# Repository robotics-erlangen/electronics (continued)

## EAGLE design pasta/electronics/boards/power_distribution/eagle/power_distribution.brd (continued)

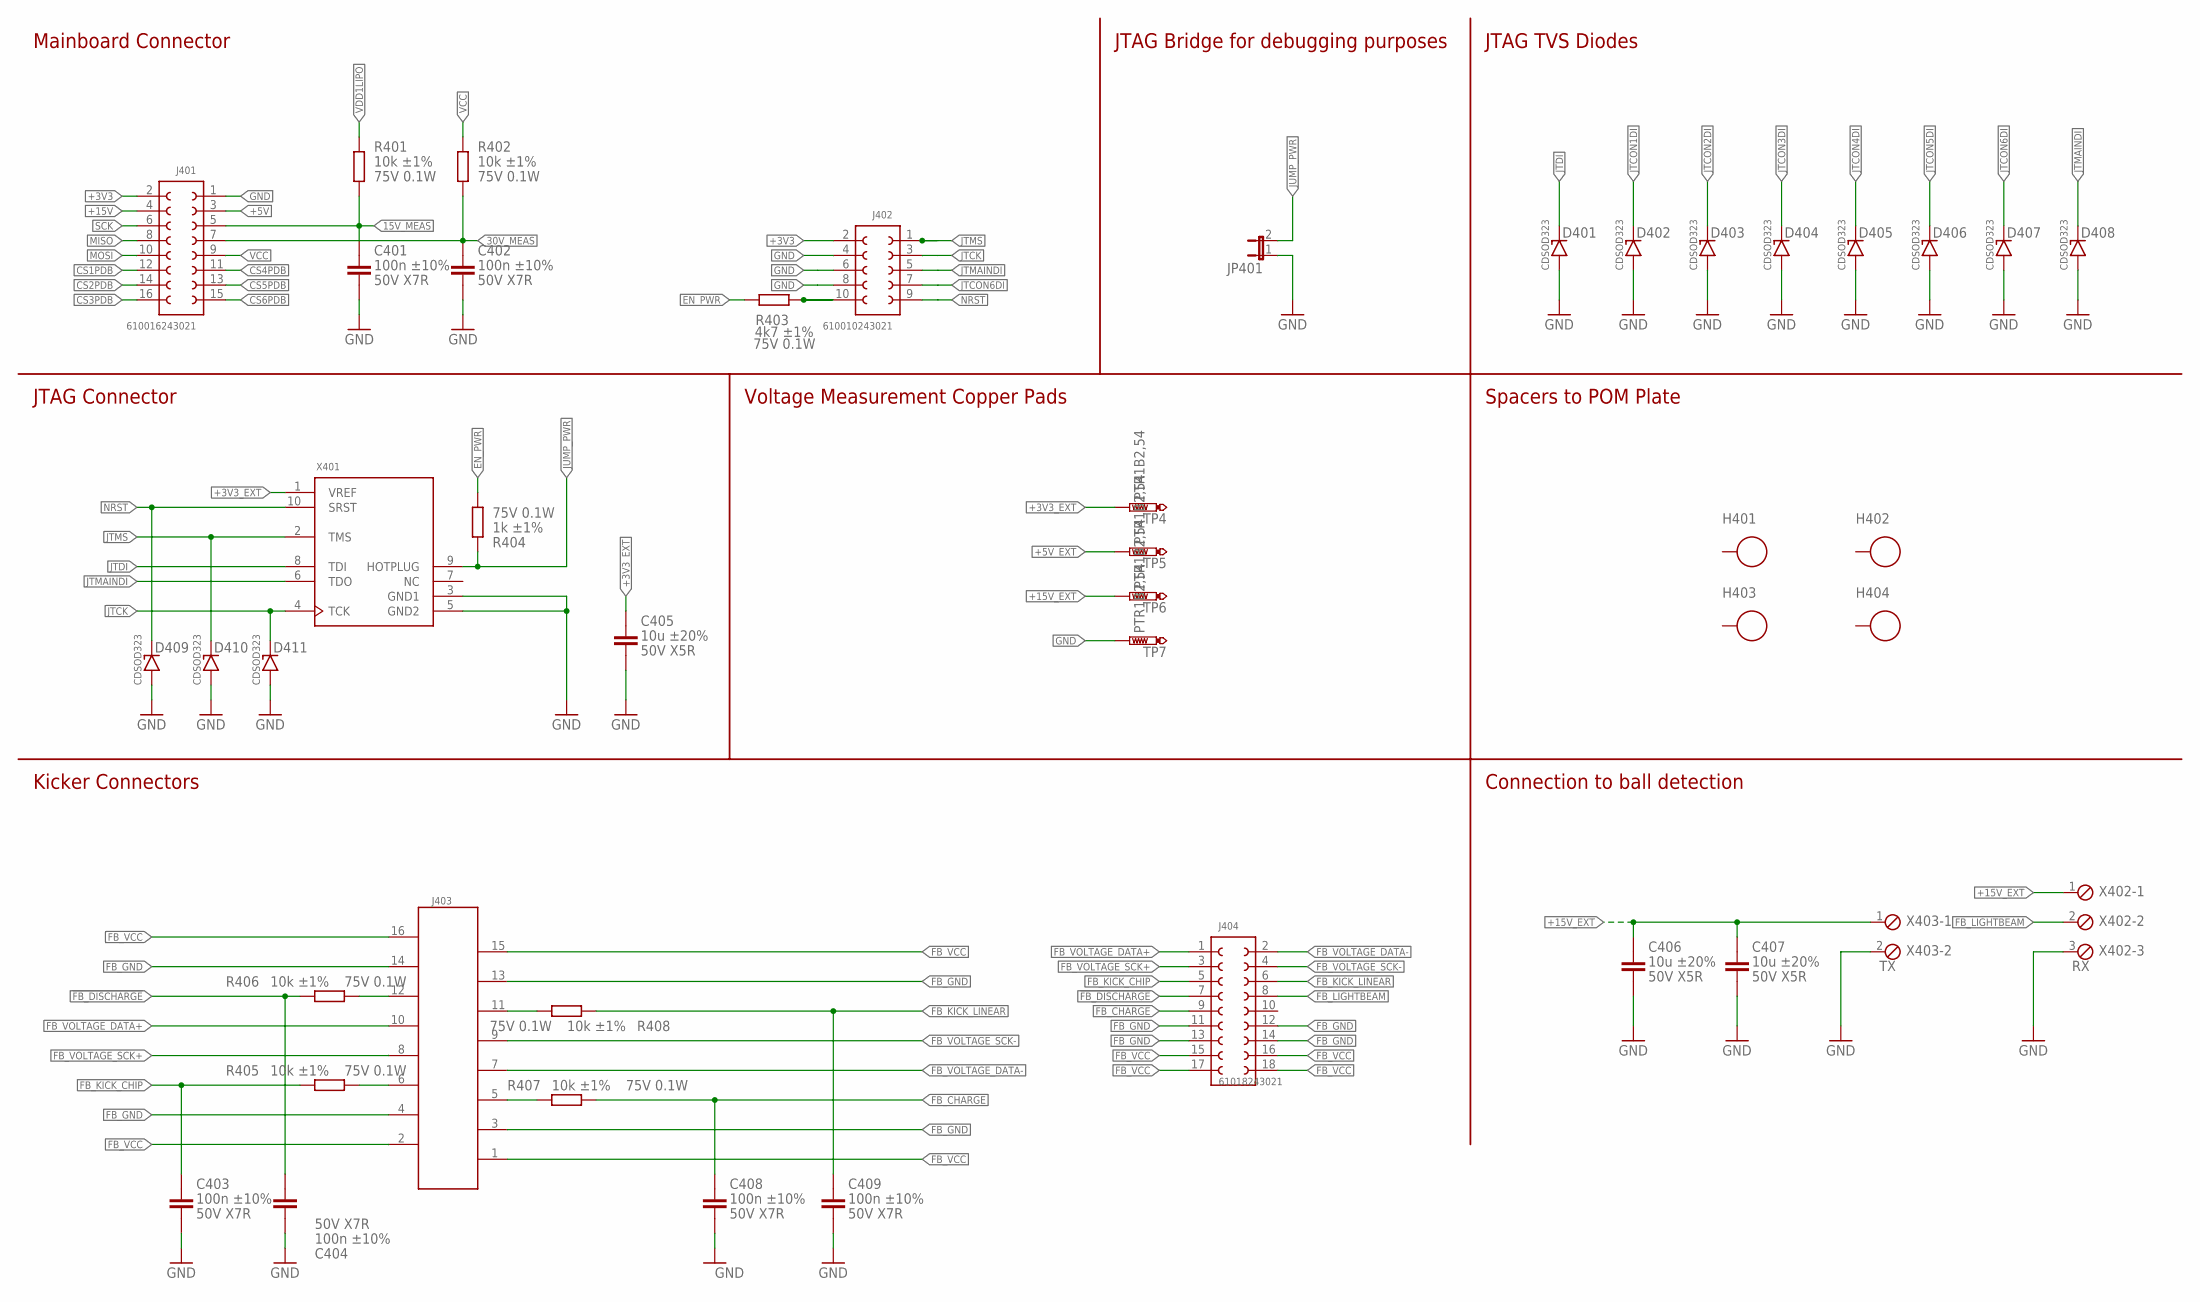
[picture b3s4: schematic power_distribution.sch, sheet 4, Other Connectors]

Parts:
C401, C402, C403, C404, C408, C409: 100n ±10% 50V X7R; C0603
C405, C406, C407: 10u ±20% 50V X5R; C1206
D401, D402, D403, D404, D405, D406, D407, D408, D409, D410, D411: CDSOD323; SOD-323; MPN CDSOD323-T03C; MOUSER 652-CDSOD323-T03C
H401, H402, H403, H404: WA-SMSI_9774360; 9774***360
J401: 610016243021; 610X16243021
J402: 610010243021; 610X10243021
J403: 690367181672
J404: 61018243021; 610X18243021
JP401: JP1E; JP1
R401, R402, R405, R406, R407, R408: 10k ±1% 75V 0.1W; R0603
R403: 4k7 ±1% 75V 0.1W; R0603
R404: 1k ±1% 75V 0.1W; R0603
TP4, TP5, TP6, TP7: PTR1B2,54; B2,54
X401: CORESIGHT-JTAG-10THD10R; ML10R; MPN 61201021721
X402: RX; 3POL254
X403: TX; 2POL254

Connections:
15V_MEAS: C401.1, J401.5 (3), R401.1
30V_MEAS: C402.1, J401.7 (4), R402.1
!FB_DISCHARGE: C404.2, J404.7 (4), R406.1
+3V3: J401.2 (16), J402.2 (10); also elsewhere on the board
+3V3_EXT: C405.1, TP4.TP, X401.1 (VREF); also elsewhere on the board
+5V: J401.3 (2); also elsewhere on the board
+5V_EXT: TP5.TP; also elsewhere on the board
+15V: J401.4 (15); also elsewhere on the board
+15V_EXT: C406.1, C407.1, TP6.TP, X402.1, X403.1; also elsewhere on the board
CS1PDB: J401.12 (11); also elsewhere on the board
CS2PDB: J401.14 (10); also elsewhere on the board
CS3PDB: J401.16 (9); also elsewhere on the board
CS4PDB: J401.11 (6); also elsewhere on the board
CS5PDB: J401.13 (7); also elsewhere on the board
CS6PDB: J401.15 (8); also elsewhere on the board
EN_PWR: R403.1, R404.1; also elsewhere on the board
FB_CHARGE: C408.1, J404.9 (5), R407.2
FB_GND: J403.3 (14), J403.4 (13), J403.13 (4), J403.14 (3), J404.11 (6), J404.12 (13), J404.13 (7), J404.14 (12)
FB_KICK_CHIP: C403.1, J404.5 (3), R405.1
FB_KICK_LINEAR: C409.1, J404.6 (16), R408.1
FB_LIGHTBEAM: J404.8 (15), X402.2
FB_VCC: J403.1 (16), J403.2 (15), J403.15 (2), J403.16 (1), J404.15 (8), J404.16 (11), J404.17 (9), J404.18 (10)
FB_VOLTAGE_DATA+: J403.10 (7), J404.1
FB_VOLTAGE_DATA-: J403.7 (10), J404.2 (18)
FB_VOLTAGE_SCK+: J403.8 (9), J404.3 (2)
FB_VOLTAGE_SCK-: J403.9 (8), J404.4 (17)
GND: C401.2, C402.2, C403.2, C404.1, C405.2, C406.2, C407.2, C408.2, C409.2, D401.2 (ANODE), D402.2 (ANODE), D403.2 (ANODE), D404.2 (ANODE), D405.2 (ANODE), D406.2 (ANODE), D407.2 (ANODE), D408.2 (ANODE), D409.2 (ANODE), D410.2 (ANODE), D411.2 (ANODE), J401.1, J402.4 (9), J402.6 (8), J402.8 (7), JP401.1, TP7.TP, X401.3 (GND1), X401.5 (GND2), X402.3, X403.2; also elsewhere on the board
JTCK: D411.1 (KATHODE), J402.3 (2), X401.4 (TCK); also elsewhere on the board
JTCON1DI: D402.1 (KATHODE); also elsewhere on the board
JTCON2DI: D403.1 (KATHODE); also elsewhere on the board
JTCON3DI: D404.1 (KATHODE); also elsewhere on the board
JTCON4DI: D405.1 (KATHODE); also elsewhere on the board
JTCON5DI: D406.1 (KATHODE); also elsewhere on the board
JTCON6DI: D407.1 (KATHODE), J402.7 (4); also elsewhere on the board
JTDI: D401.1 (KATHODE), X401.8 (TDI); also elsewhere on the board
JTMAINDI: D408.1 (KATHODE), J402.5 (3), X401.6 (TDO)
JTMS: D410.1 (KATHODE), J402.1, X401.2 (TMS); also elsewhere on the board
JUMP_PWR: JP401.2, R404.2, X401.9 (HOTPLUG)
MISO: J401.8 (13); also elsewhere on the board
MOSI: J401.10 (12); also elsewhere on the board
unnamed: J403.5 (12), R407.1
unnamed: J403.6 (11), R405.2
unnamed: J402.10 (6), R403.2
unnamed: J403.11 (6), R408.2
unnamed: J403.12 (5), R406.2
NRST: D409.1 (KATHODE), J402.9 (5), X401.10 (SRST); also elsewhere on the board
SCK: J401.6 (14); also elsewhere on the board
VCC: J401.9 (5), R402.2; also elsewhere on the board
VDD1LIPO: R401.2; also elsewhere on the board

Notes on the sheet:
JTAG Connector
Mainboard Connector
JTAG TVS Diodes
Voltage Measurement Copper Pads
Spacers to POM Plate
JTAG Bridge for debugging purposes
Kicker Connectors
Connection to ball detection

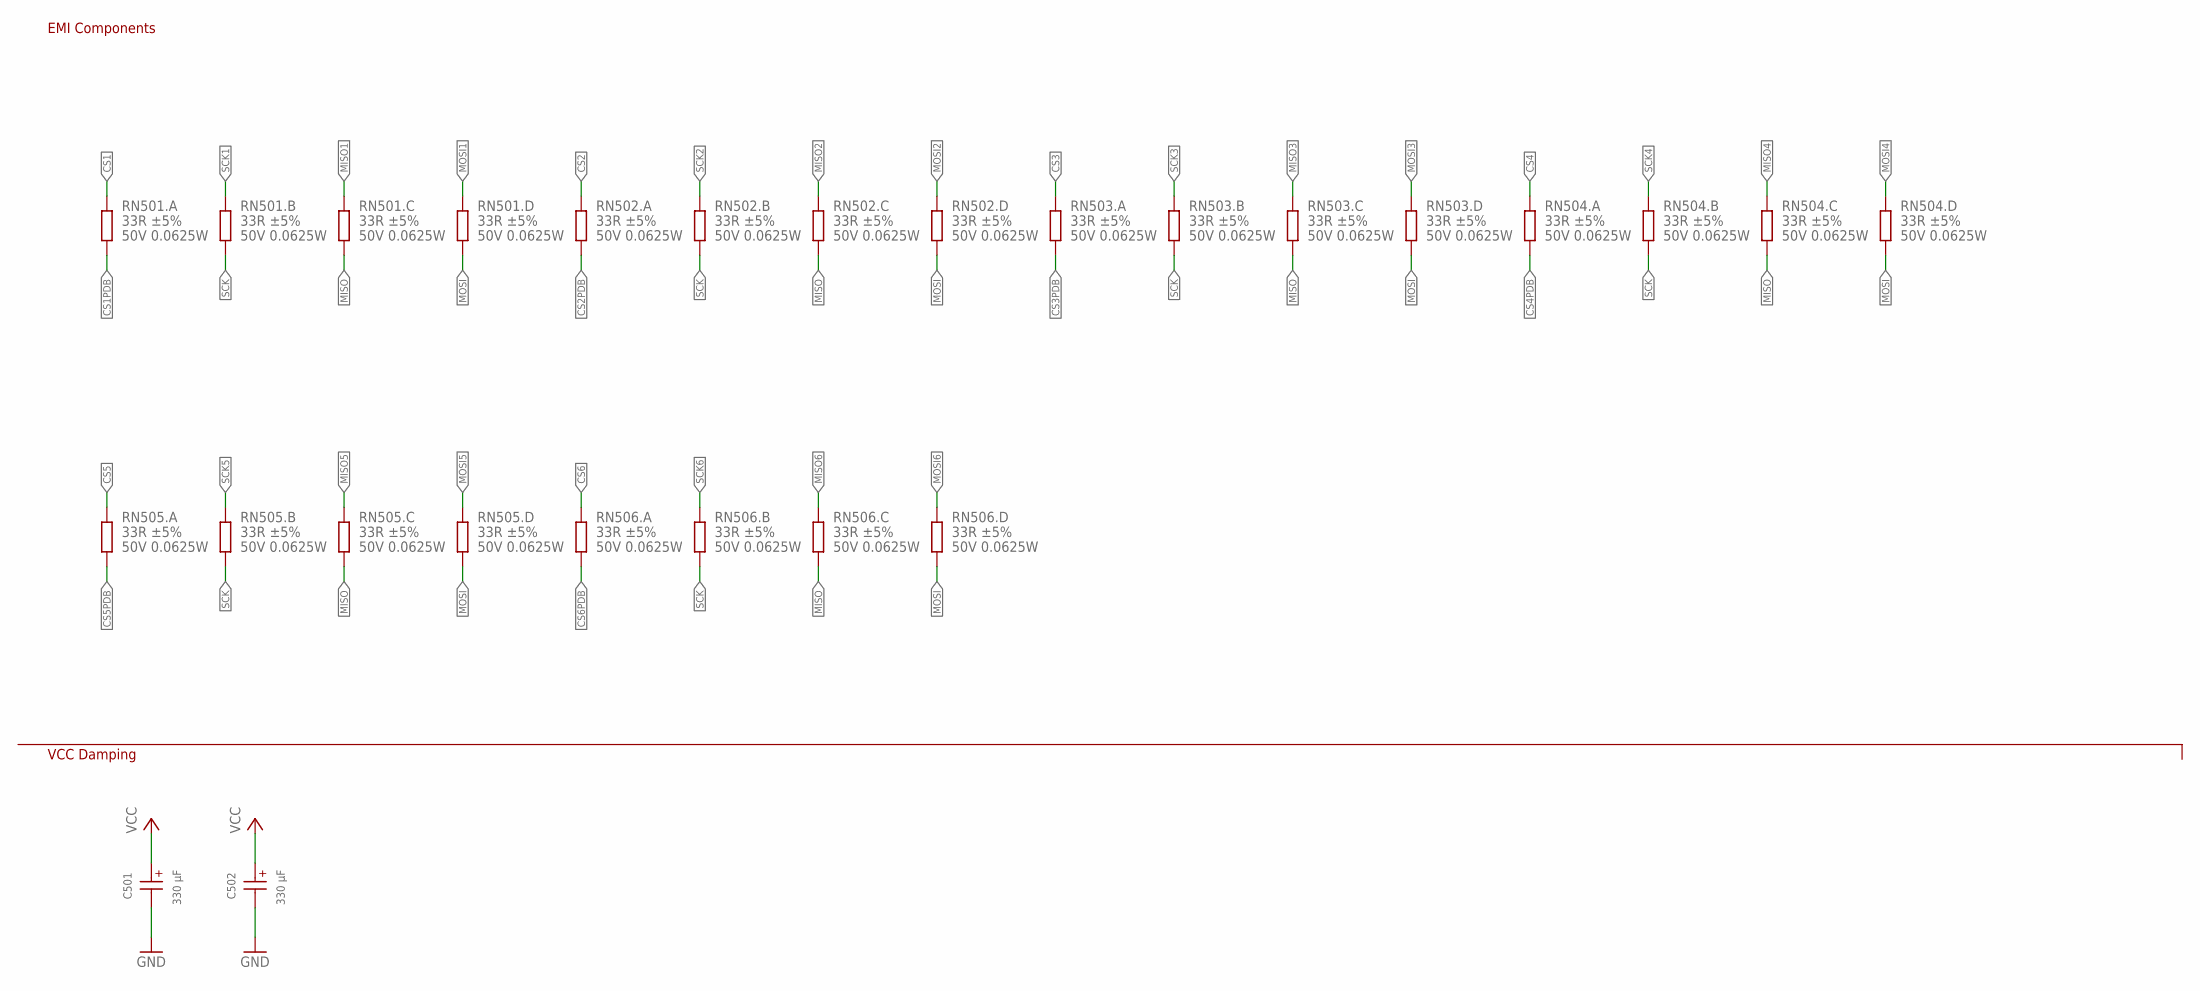
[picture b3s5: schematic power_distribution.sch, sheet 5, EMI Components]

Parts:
C501, C502: 330 µF; WCAP-AS5H_10X10.5(DXL)
RN501, RN502, RN503, RN504, RN505, RN506: 33R ±5% 50V 0.0625W; EXB38

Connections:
CS1: RN501.1-2 (2); also elsewhere on the board
CS1PDB: RN501.1-1 (1); also elsewhere on the board
CS2: RN502.1-2 (2); also elsewhere on the board
CS2PDB: RN502.1-1 (1); also elsewhere on the board
CS3: RN503.1-2 (2); also elsewhere on the board
CS3PDB: RN503.1-1 (1); also elsewhere on the board
CS4: RN504.1-2 (2); also elsewhere on the board
CS4PDB: RN504.1-1 (1); also elsewhere on the board
CS5: RN505.1-2 (2); also elsewhere on the board
CS5PDB: RN505.1-1 (1); also elsewhere on the board
CS6: RN506.1-2 (2); also elsewhere on the board
CS6PDB: RN506.1-1 (1); also elsewhere on the board
GND: C501.2 (-), C502.2 (-); also elsewhere on the board
MISO: RN501.3-1 (1), RN502.3-1 (1), RN503.3-1 (1), RN504.3-1 (1), RN505.3-1 (1), RN506.3-1 (1); also elsewhere on the board
MISO1: RN501.3-2 (2); also elsewhere on the board
MISO2: RN502.3-2 (2); also elsewhere on the board
MISO3: RN503.3-2 (2); also elsewhere on the board
MISO4: RN504.3-2 (2); also elsewhere on the board
MISO5: RN505.3-2 (2); also elsewhere on the board
MISO6: RN506.3-2 (2); also elsewhere on the board
MOSI: RN501.4-1 (1), RN502.4-1 (1), RN503.4-1 (1), RN504.4-1 (1), RN505.4-1 (1), RN506.4-1 (1); also elsewhere on the board
MOSI1: RN501.4-2 (2); also elsewhere on the board
MOSI2: RN502.4-2 (2); also elsewhere on the board
MOSI3: RN503.4-2 (2); also elsewhere on the board
MOSI4: RN504.4-2 (2); also elsewhere on the board
MOSI5: RN505.4-2 (2); also elsewhere on the board
MOSI6: RN506.4-2 (2); also elsewhere on the board
SCK: RN501.2-1 (1), RN502.2-1 (1), RN503.2-1 (1), RN504.2-1 (1), RN505.2-1 (1), RN506.2-1 (1); also elsewhere on the board
SCK1: RN501.2-2 (2); also elsewhere on the board
SCK2: RN502.2-2 (2); also elsewhere on the board
SCK3: RN503.2-2 (2); also elsewhere on the board
SCK4: RN504.2-2 (2); also elsewhere on the board
SCK5: RN505.2-2 (2); also elsewhere on the board
SCK6: RN506.2-2 (2); also elsewhere on the board
VCC: C501.1 (+), C502.1 (+); also elsewhere on the board

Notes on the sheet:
EMI Components
VCC Damping

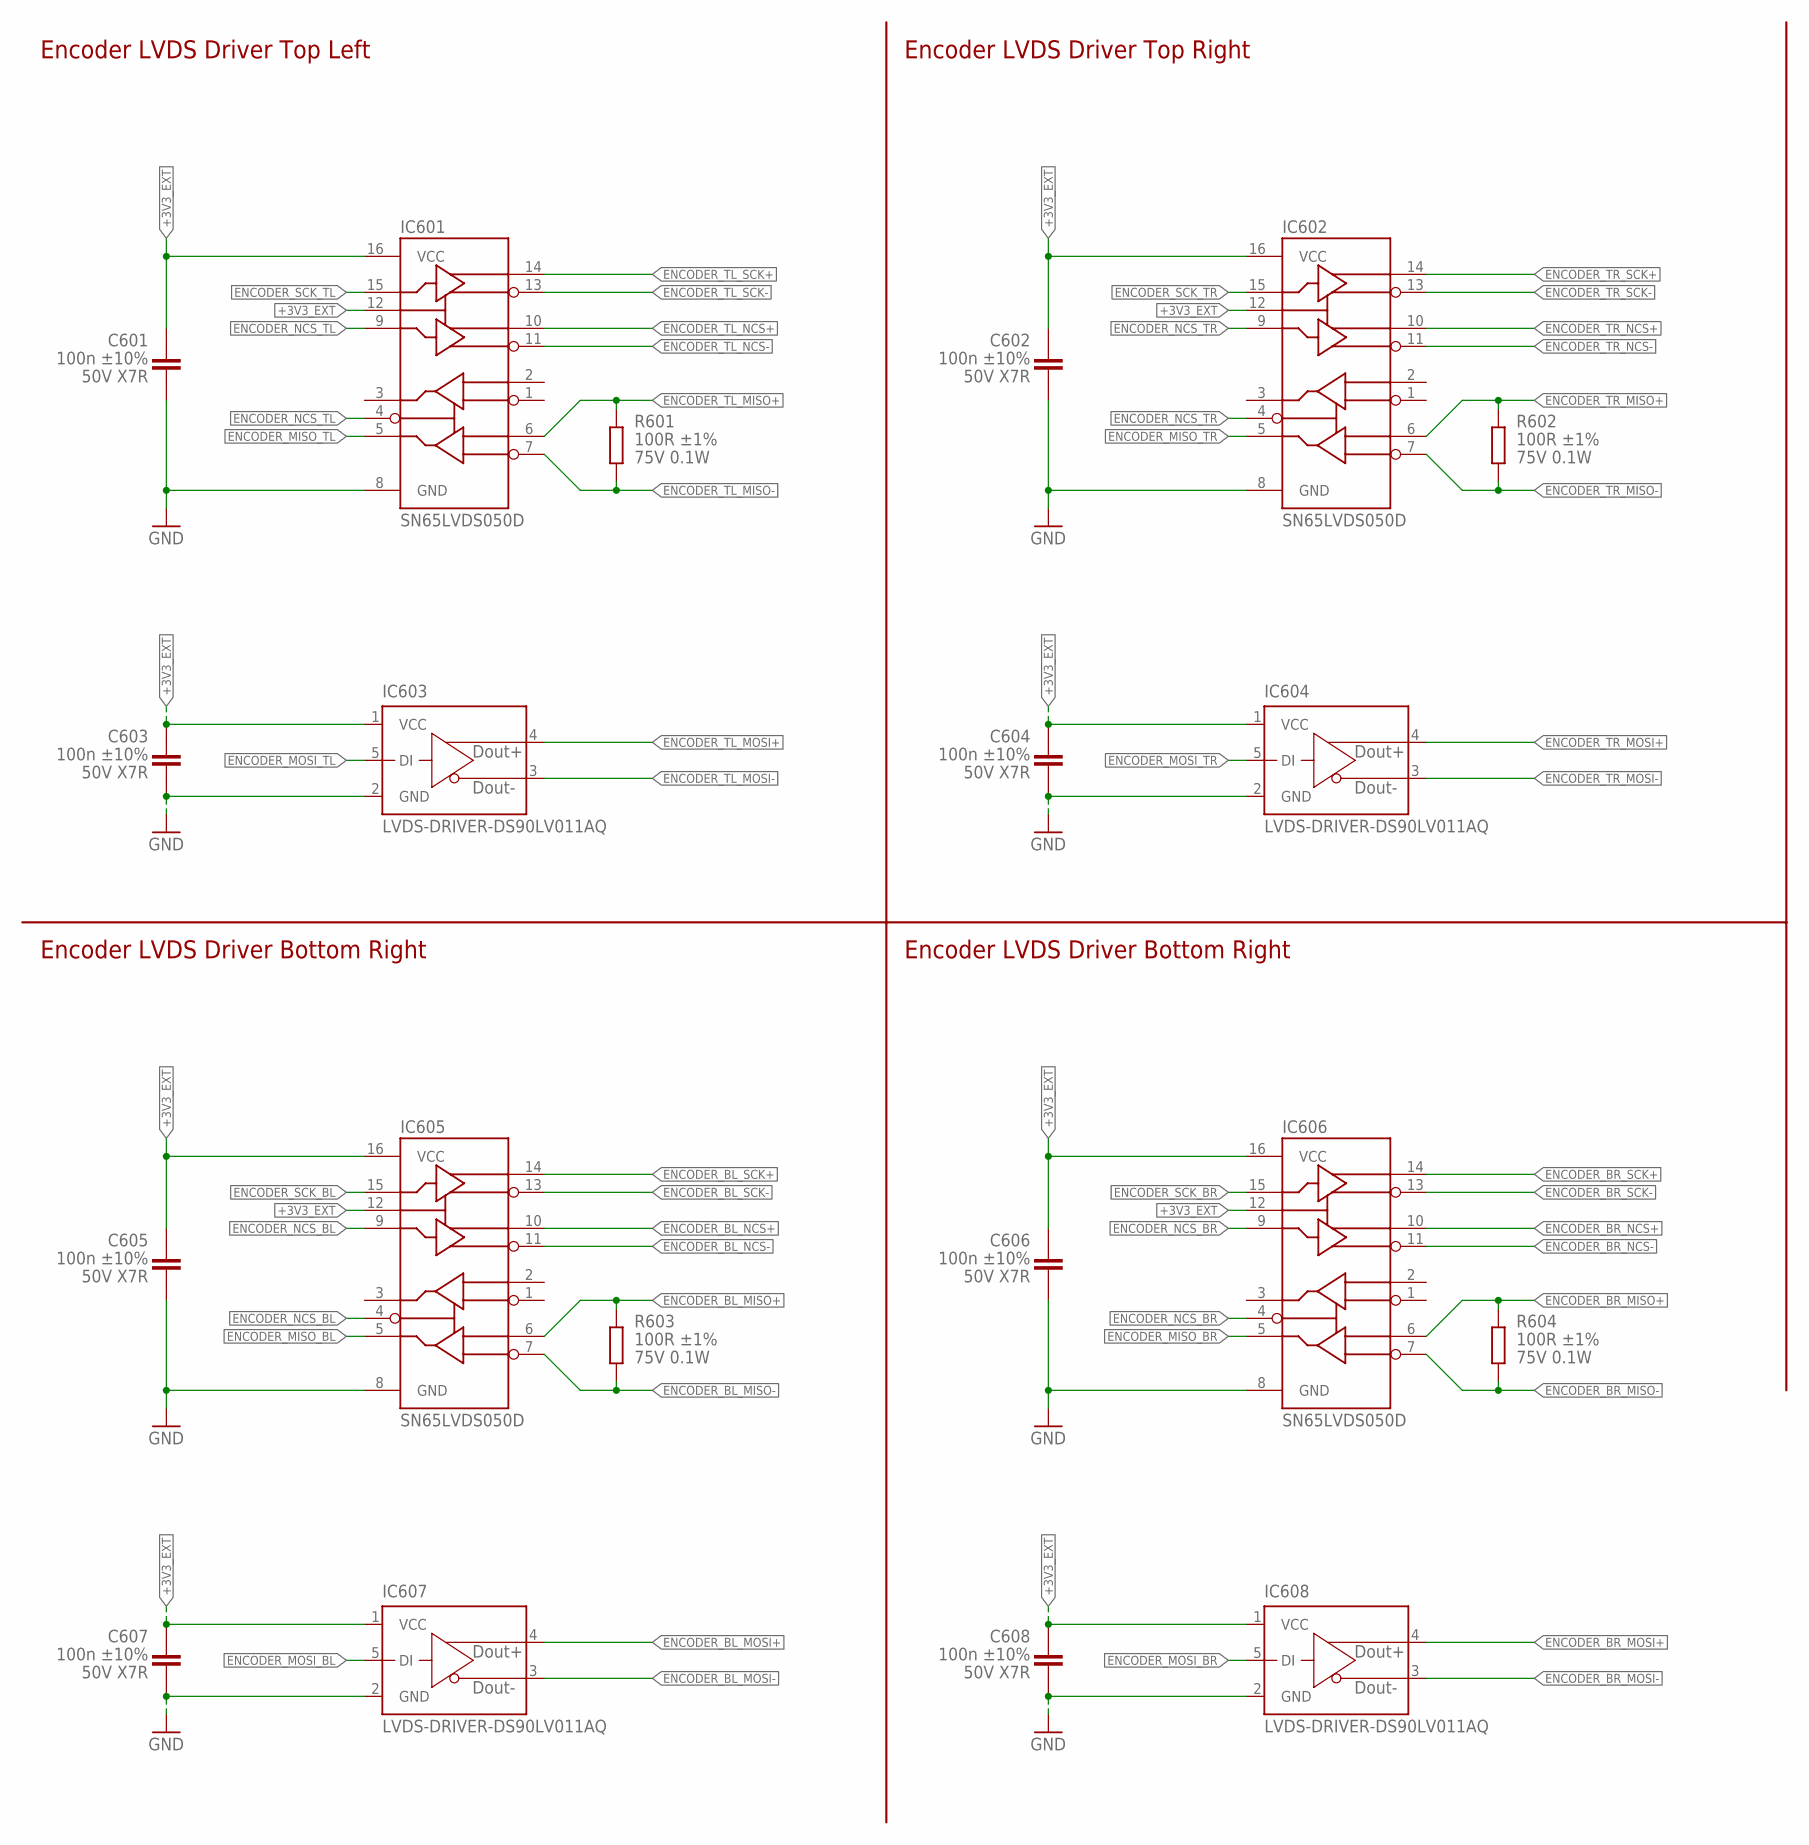
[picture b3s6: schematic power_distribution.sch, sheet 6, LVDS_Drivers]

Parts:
C601, C602, C603, C604, C605, C606, C607, C608: 100n ±10% 50V X7R; C0603
IC601, IC602, IC605, IC606: SN65LVDS050D; SO16
IC603, IC604, IC607, IC608: LVDS-DRIVER-DS90LV011AQ; SOT23-5
R601, R602, R603, R604: 100R ±1% 75V 0.1W; R0603

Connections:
+3V3_EXT: C601.1, C602.1, C603.1, C604.1, C605.1, C606.1, C607.1, C608.1, IC601.12 (DE), IC601.16 (VCC), IC602.12 (DE), IC602.16 (VCC), IC603.1 (VCC), IC604.1 (VCC), IC605.12 (DE), IC605.16 (VCC), IC606.12 (DE), IC606.16 (VCC), IC607.1 (VCC), IC608.1 (VCC); also elsewhere on the board
ENCODER_BL_MISO+: IC605.6 (2A), R603.2; also elsewhere on the board
ENCODER_BL_MISO-: IC605.7 (2B), R603.1; also elsewhere on the board
ENCODER_BL_MOSI+: IC607.4 (DOUT+); also elsewhere on the board
ENCODER_BL_MOSI-: IC607.3 (DOUT-); also elsewhere on the board
ENCODER_BL_NCS+: IC605.10 (2Y); also elsewhere on the board
ENCODER_BL_NCS-: IC605.11 (2Z); also elsewhere on the board
ENCODER_BL_SCK+: IC605.14 (1Y); also elsewhere on the board
ENCODER_BL_SCK-: IC605.13 (1Z); also elsewhere on the board
ENCODER_BR_MISO+: IC606.6 (2A), R604.2; also elsewhere on the board
ENCODER_BR_MISO-: IC606.7 (2B), R604.1; also elsewhere on the board
ENCODER_BR_MOSI+: IC608.4 (DOUT+); also elsewhere on the board
ENCODER_BR_MOSI-: IC608.3 (DOUT-); also elsewhere on the board
ENCODER_BR_NCS+: IC606.10 (2Y); also elsewhere on the board
ENCODER_BR_NCS-: IC606.11 (2Z); also elsewhere on the board
ENCODER_BR_SCK+: IC606.14 (1Y); also elsewhere on the board
ENCODER_BR_SCK-: IC606.13 (1Z); also elsewhere on the board
ENCODER_MISO_BL: IC605.5 (2R); also elsewhere on the board
ENCODER_MISO_BR: IC606.5 (2R); also elsewhere on the board
ENCODER_MISO_TL: IC601.5 (2R); also elsewhere on the board
ENCODER_MISO_TR: IC602.5 (2R); also elsewhere on the board
ENCODER_MOSI_BL: IC607.5 (DI); also elsewhere on the board
ENCODER_MOSI_BR: IC608.5 (DI); also elsewhere on the board
ENCODER_MOSI_TL: IC603.5 (DI); also elsewhere on the board
ENCODER_MOSI_TR: IC604.5 (DI); also elsewhere on the board
ENCODER_NCS_BL: IC605.4 (RE), IC605.9 (2D); also elsewhere on the board
ENCODER_NCS_BR: IC606.4 (RE), IC606.9 (2D); also elsewhere on the board
ENCODER_NCS_TL: IC601.4 (RE), IC601.9 (2D); also elsewhere on the board
ENCODER_NCS_TR: IC602.4 (RE), IC602.9 (2D); also elsewhere on the board
ENCODER_SCK_BL: IC605.15 (1D); also elsewhere on the board
ENCODER_SCK_BR: IC606.15 (1D); also elsewhere on the board
ENCODER_SCK_TL: IC601.15 (1D); also elsewhere on the board
ENCODER_SCK_TR: IC602.15 (1D); also elsewhere on the board
ENCODER_TL_MISO+: IC601.6 (2A), R601.2; also elsewhere on the board
ENCODER_TL_MISO-: IC601.7 (2B), R601.1; also elsewhere on the board
ENCODER_TL_MOSI+: IC603.4 (DOUT+); also elsewhere on the board
ENCODER_TL_MOSI-: IC603.3 (DOUT-); also elsewhere on the board
ENCODER_TL_NCS+: IC601.10 (2Y); also elsewhere on the board
ENCODER_TL_NCS-: IC601.11 (2Z); also elsewhere on the board
ENCODER_TL_SCK+: IC601.14 (1Y); also elsewhere on the board
ENCODER_TL_SCK-: IC601.13 (1Z); also elsewhere on the board
ENCODER_TR_MISO+: IC602.6 (2A), R602.2; also elsewhere on the board
ENCODER_TR_MISO-: IC602.7 (2B), R602.1; also elsewhere on the board
ENCODER_TR_MOSI+: IC604.4 (DOUT+); also elsewhere on the board
ENCODER_TR_MOSI-: IC604.3 (DOUT-); also elsewhere on the board
ENCODER_TR_NCS+: IC602.10 (2Y); also elsewhere on the board
ENCODER_TR_NCS-: IC602.11 (2Z); also elsewhere on the board
ENCODER_TR_SCK+: IC602.14 (1Y); also elsewhere on the board
ENCODER_TR_SCK-: IC602.13 (1Z); also elsewhere on the board
GND: C601.2, C602.2, C603.2, C604.2, C605.2, C606.2, C607.2, C608.2, IC601.8 (GND), IC602.8 (GND), IC603.2 (GND), IC604.2 (GND), IC605.8 (GND), IC606.8 (GND), IC607.2 (GND), IC608.2 (GND); also elsewhere on the board

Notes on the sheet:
Encoder LVDS Driver Top Left
Encoder LVDS Driver Top Right
Encoder LVDS Driver Bottom Right

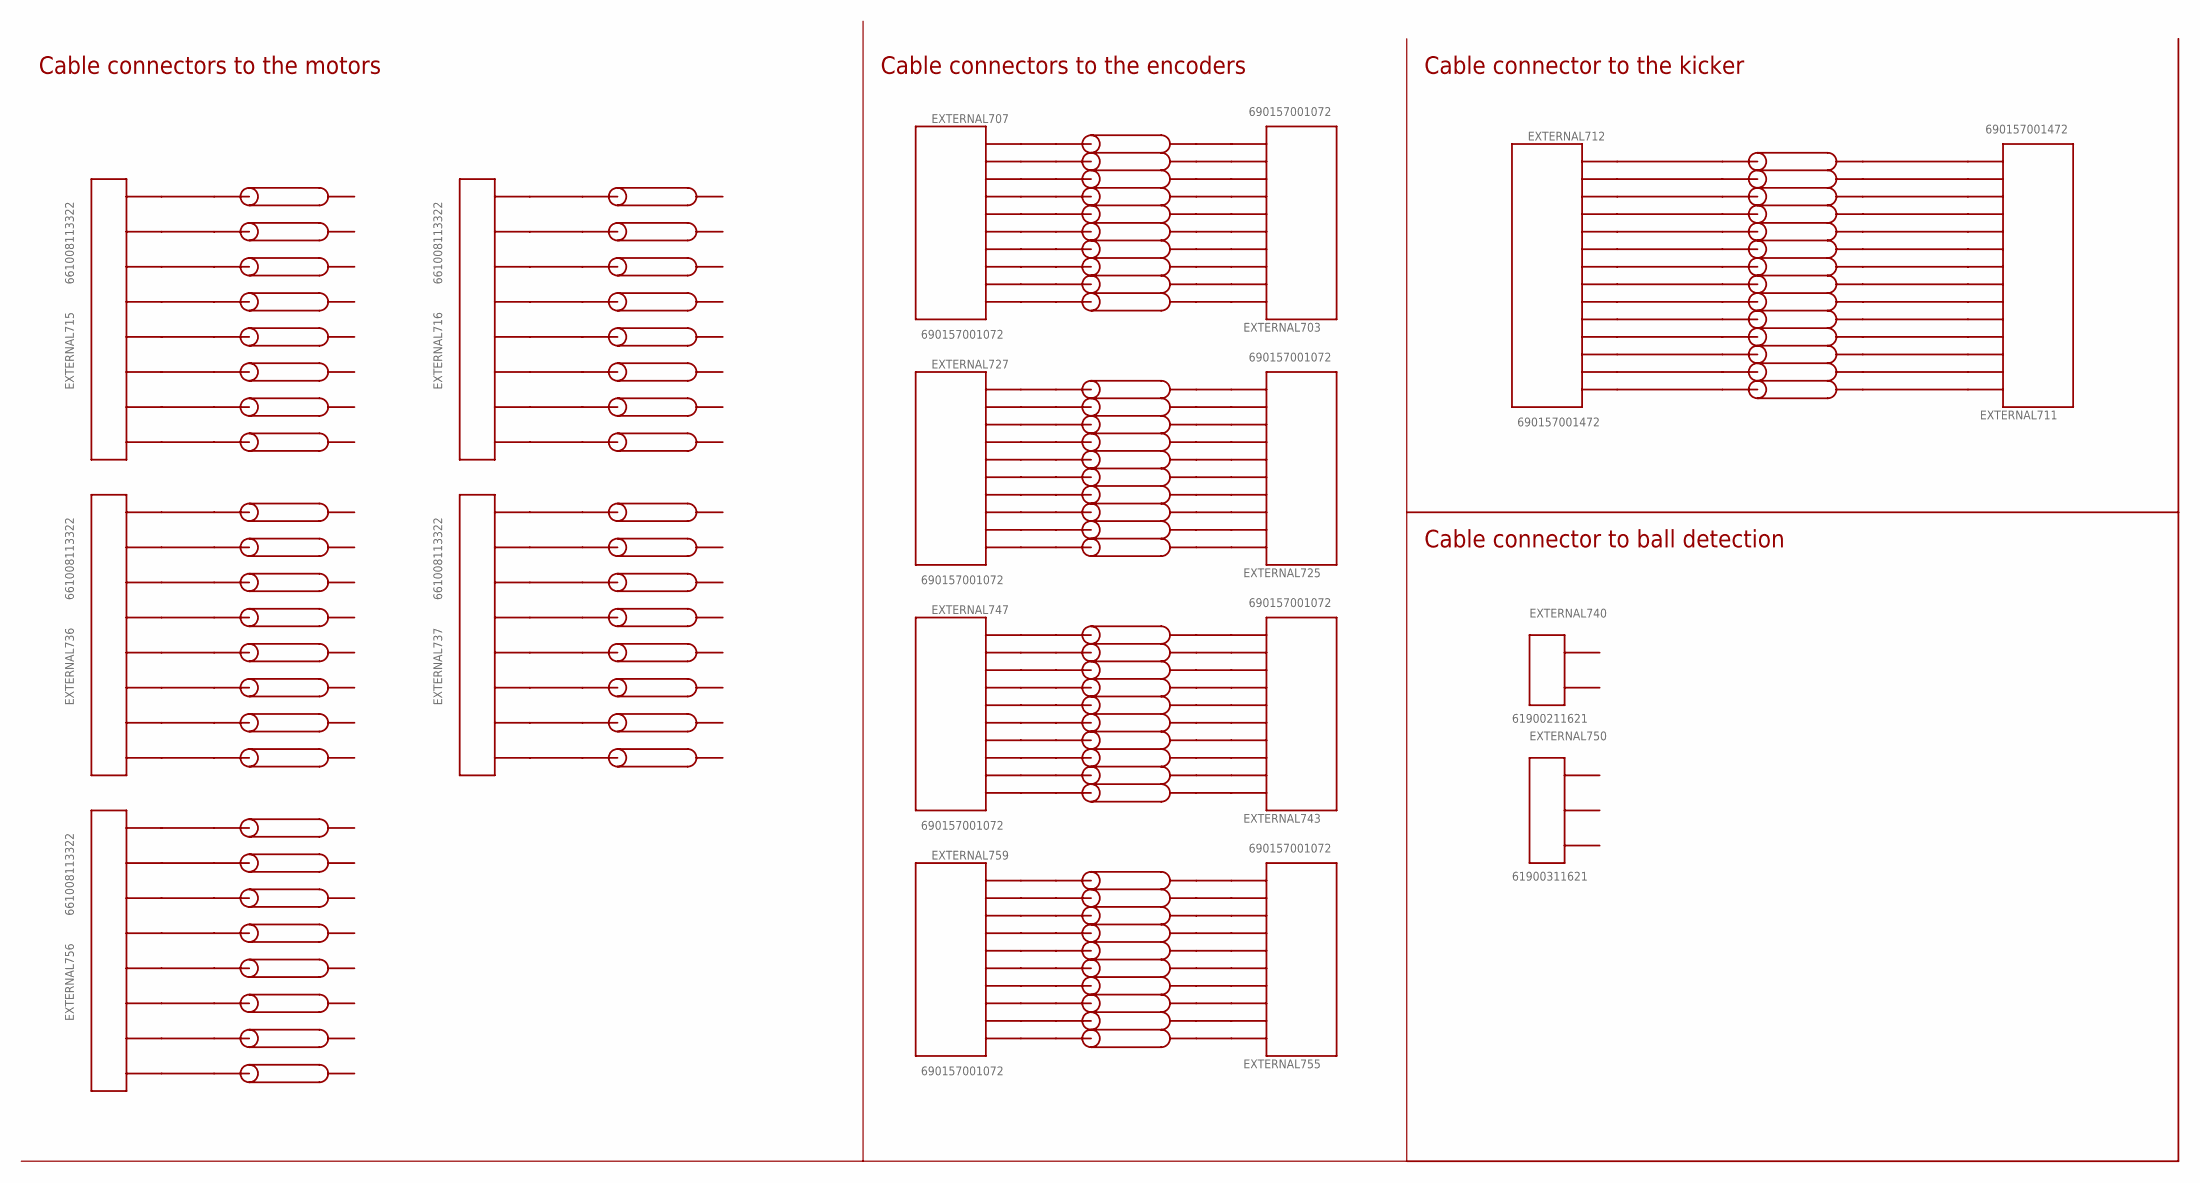
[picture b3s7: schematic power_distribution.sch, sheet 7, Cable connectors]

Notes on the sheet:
Cable connectors to the motors
Cable connectors to the encoders
Cable connector to the kicker
Cable connector to ball detection
